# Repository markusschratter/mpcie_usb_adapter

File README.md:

# mPCIe USB Adapter

The mPCIe USB Adapter enables connecting mPCIe modules (WiFi, Bluetooth, GNSS, etc.) to a host system via USB 2.0. The board features power regulation from 5V to 3.3V, comprehensive ESD protection on USB and signal lines, and RF connectors for antenna connections. Status LEDs provide visual feedback for power indication.

- mPCIe connector for module connection
- USB 2.0 Type-C connector for host connectivity
- 3.3V voltage regulator (LD1117S33TR) for power regulation
- ESD protection diodes for USB and signal lines
- Status LEDs (Kingbright AA4040SURSK) for power indication
- SMA connectors for RF/antenna connections
- Coaxial connectors for additional RF connections

## Overview

The mPCIe USB Adapter board allows connecting mPCIe modules (such as WiFi, Bluetooth, or GNSS modules) to a host system via USB.

| Parameter | Value |
|-----------|-------|
| Input Voltage | 5V DC (via USB) |
| Output Voltage | 3.3V DC (regulated) |
| USB Standard | USB 2.0 Type-C |
| Connector Type | mPCIe (full-size) |
| RF Connectors | 2x SMA, 2x Coaxial |

## Project Structure

```
mpcie_usb_adapter/
├── mpcie_usb_adapter.kicad_sch
├── mpcie_usb_adapter.kicad_pcb
├── mpcie_usb_adapter.kicad_pro
├── mpcie_usb_adapter.png
└── 3dmodels/                 # 3D models for components
    ├── mpcie_usb_adapter.step
    └── mpcie_usb_adapter.stl
```

## Components

| Component | Qty | Part Number | Description |
|-----------|-----|-------------|-------------|
| mPCIe Connector | 1 | [MM60-52B1-G1-R850](https://www.jae.com/de/connectors/series/detail/product/id=68908) ([Mouser](https://www.mouser.at/ProductDetail/JAE-Electronics/MM60-52B1-G1-R850?qs=LBWgzgGgPo%252BV%252BU%2FdH2aUqA%3D%3D)) | mPCIe full-size connector |
| USB Connector | 1 | [USB4105-GF-A](https://gct.co/connector/usb4105) ([Mouser](https://www.mouser.at/ProductDetail/GCT/USB4105-GF-A?qs=KUoIvG%2F9IlY%2FMLlBMpStpA%3D%3D)) | USB 2.0 Type-C connector |
| Voltage Regulator | 1 | [LD1117S33TR](https://www.st.com/resource/en/datasheet/ld1117.pdf) ([Mouser](https://www.mouser.at/ProductDetail/STMicroelectronics/LD1117S33TR?qs=edoyzKMbmhntQZx4BFmoqw%3D%3D)) | 3.3V LDO regulator |
| SMA Connector | 2 | [SMA-J-P-H-ST-EM1](https://www.samtec.com/de/products/sma-j-p-h-st-em1) ([Mouser](https://www.mouser.at/ProductDetail/Samtec/SMA-J-P-H-ST-EM1?qs=92ilVni64gwBP41DrnuA8Q%3D%3D)) | SMA RF connector (Samtec) |
| UFL Connector | 2 | [U.FL-R-SMT-110](https://4donline.ihs.com/images/VipMasterIC/IC/HIRO/HIROS10696/HIROS08829-1.pdf?hkey=CECEF36DEECDED6468708AAF2E19C0C6) ([Mouser](https://www.mouser.at/ProductDetail/Hirose-Connector/U.FL-R-SMT-110?qs=kL1ClTr6oBoOdtqlGQpQrQ%3D%3D)) | UFL coaxial RF connector (Hirose) |
| LED | 1 | [AA4040SURSK](https://www.kingbrightusa.com/images/catalog/spec/aa4040sursk.pdf) ([Mouser](https://www.mouser.com/ProductDetail/Kingbright/AA4040SURSK)) | Status LED (Kingbright) |
| ESD Protection | 2 | ESD321 | ESD protection diode |
| ESD Protection | 1 | ESD441 | ESD protection diode |
| Resistors (5.1kΩ) | 2 | R_0805_2012Metric | LED current limiting |
| Resistor (750Ω) | 1 | R_0805_2012Metric | Current limiting |
| Capacitors (100nF) | 6 | C_0805_2012Metric | Decoupling capacitors |
| Capacitors (10µF) | 2 | C_0805_2012Metric | Filtering capacitors |

## Design Files

All design files are in KiCad 9.0 format (`.kicad_sch`, `.kicad_pcb`, `.kicad_pro`). 3D STEP and STL models of the board and components are included in the `3dmodels/` directory.

**3D Board Models:**
- [STEP file](3dmodels/mpcie_usb_adapter.step) - 3D model for mechanical design
- [STL file](3dmodels/mpcie_usb_adapter.stl) - 3D model for 3D printing

**Assembly Notes**: Ensure proper ESD handling during assembly, verify LED polarity, use appropriate USB cable specifications, follow RF connector assembly guidelines.

## Acknowledgments

Thanks to **Matteo Valentini** for review and modifications.

## License

Licensed under the Apache License, Version 2.0. See [LICENSE](LICENSE) file for details.

## Contributing

Contributions are welcome! Please feel free to submit issues or pull requests.

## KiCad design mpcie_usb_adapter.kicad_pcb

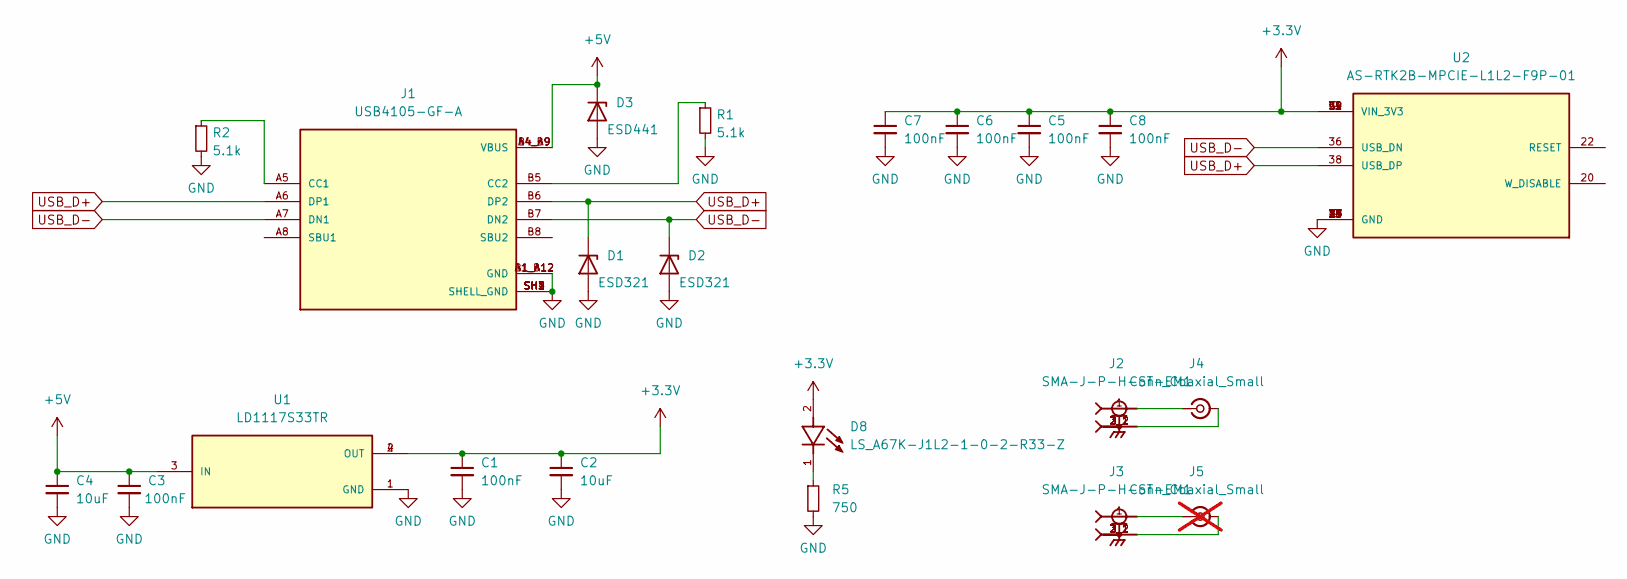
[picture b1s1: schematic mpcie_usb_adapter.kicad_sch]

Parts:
C1, C3, C5, C6, C7, C8: 100nF; C_0805_2012Metric
C2, C4: 10uF; C_0805_2012Metric
D1, D2: ESD321; D_SOD-523
D3: ESD441; D_SOD-523
D8: LS_A67K-J1L2-1-0-2-R33-Z; LED_LS_A67K-J1L2-1-0-2-R33-Z; PARTREV 1.5
J1: USB4105-GF-A; GCT_USB4105-GF-A; PARTREV B4
J2, J3: SMA-J-P-H-ST-EM1; SAMTEC_SMA-J-P-H-ST-EM1; PARTREV G
J4: Conn_Coaxial_Small; U.FL_Hirose_U.FL-R-SMT-1_Vertical
J5: Conn_Coaxial_Small; U.FL_Hirose_U.FL-R-SMT-1_Vertical; not fitted
R1, R2: 5.1k; R_0805_2012Metric
R5: 750; R_0805_2012Metric
U1: LD1117S33TR; SOT230P700X180-4N
U2: AS-RTK2B-MPCIE-L1L2-F9P-01; MODULE_AS-RTK2B-MPCIE-L1L2-F9P-01; PARTREV D

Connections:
+3.3V: C1.1, C2.1, C5.1, C6.1, C7.1, C8.1, D8.2, U1.2 (OUT), U1.4 (OUT), U2.2 (VIN_3V3), U2.24 (VIN_3V3), U2.39 (VIN_3V3), U2.41 (VIN_3V3), U2.52 (VIN_3V3)
+5V: C3.1, C4.1, D3.1 (K), J1.A4_B9 (VBUS), J1.B4_A9 (VBUS), U1.3 (IN)
GND: C1.2, C2.2, C3.2, C4.2, C5.2, C6.2, C7.2, C8.2, D1.2 (A), D2.2 (A), D3.2 (A), J1.A1_B12 (GND), J1.B1_A12 (GND), J1.SH1 (SHELL_GND), J1.SH2 (SHELL_GND), J1.SH3 (SHELL_GND), J1.SH4 (SHELL_GND), R1.2, R2.2, R5.2, U1.1 (GND), U2.9 (GND), U2.15 (GND), U2.21 (GND), U2.27 (GND), U2.29 (GND), U2.35 (GND), U2.37 (GND), U2.43 (GND)
unnamed: D8.1, R5.1
unnamed: J1.A5 (CC1), R2.1
unnamed: J1.B5 (CC2), R1.1
unnamed: J2.2_1, J2.2_2, J2.3_1, J2.3_2, J4.2 (Ext)
unnamed: J2.1, J4.1 (In)
unnamed: J3.2_1, J3.2_2, J3.3_1, J3.3_2, J5.2 (Ext)
unnamed: J3.1, J5.1 (In)
USB_D+: D1.1 (K), J1.A6 (DP1), J1.B6 (DP2), U2.38 (USB_DP)
USB_D-: D2.1 (K), J1.A7 (DN1), J1.B7 (DN2), U2.36 (USB_DN)

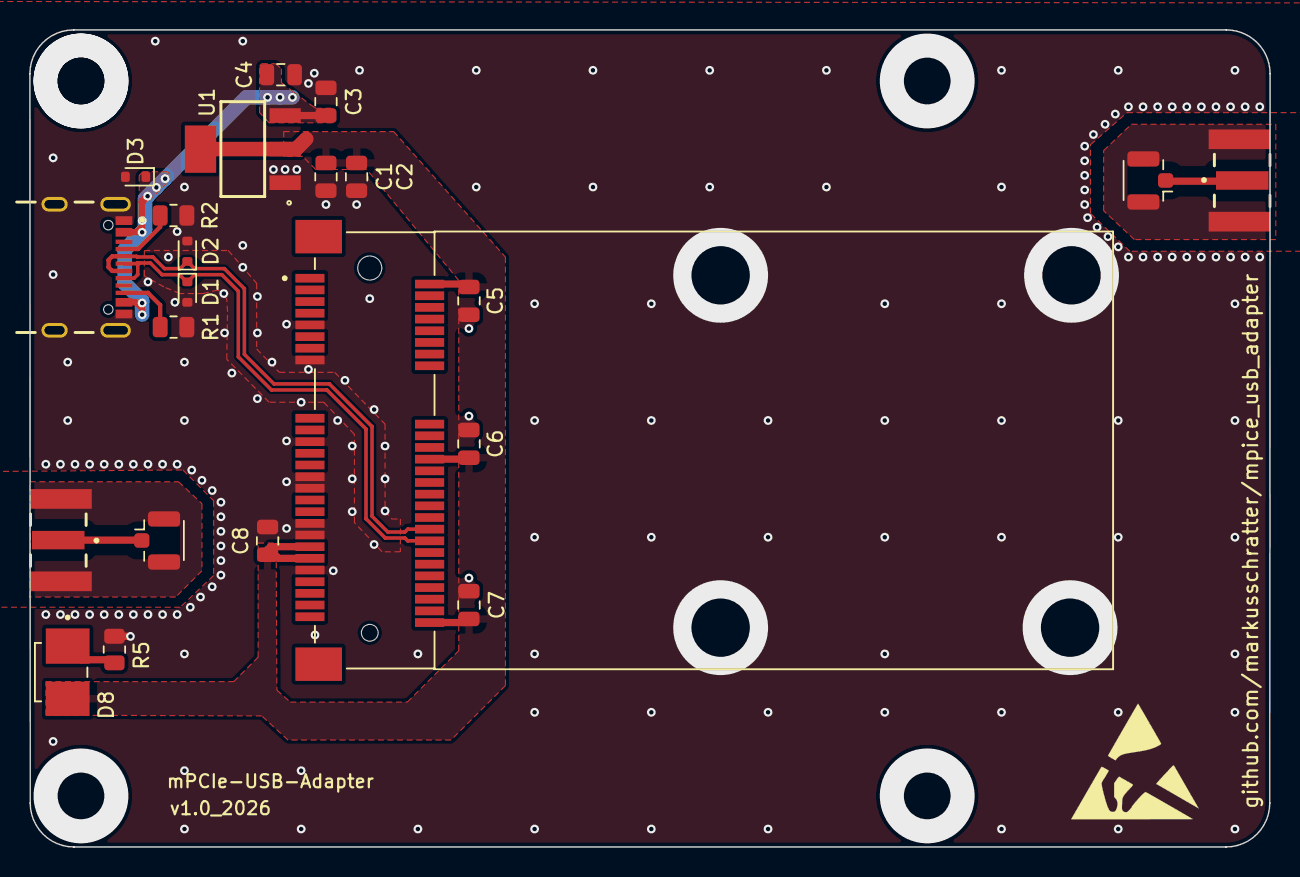
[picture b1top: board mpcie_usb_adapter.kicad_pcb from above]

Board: 2 copper layers, 85.0 x 56.0 mm, 22 parts (0 on the bottom side), 12 nets.

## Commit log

2026-02-21 integrated updates from Matteo and added 3d models
2026-02-22 added README.md and 3d models of the board (step,stl)
